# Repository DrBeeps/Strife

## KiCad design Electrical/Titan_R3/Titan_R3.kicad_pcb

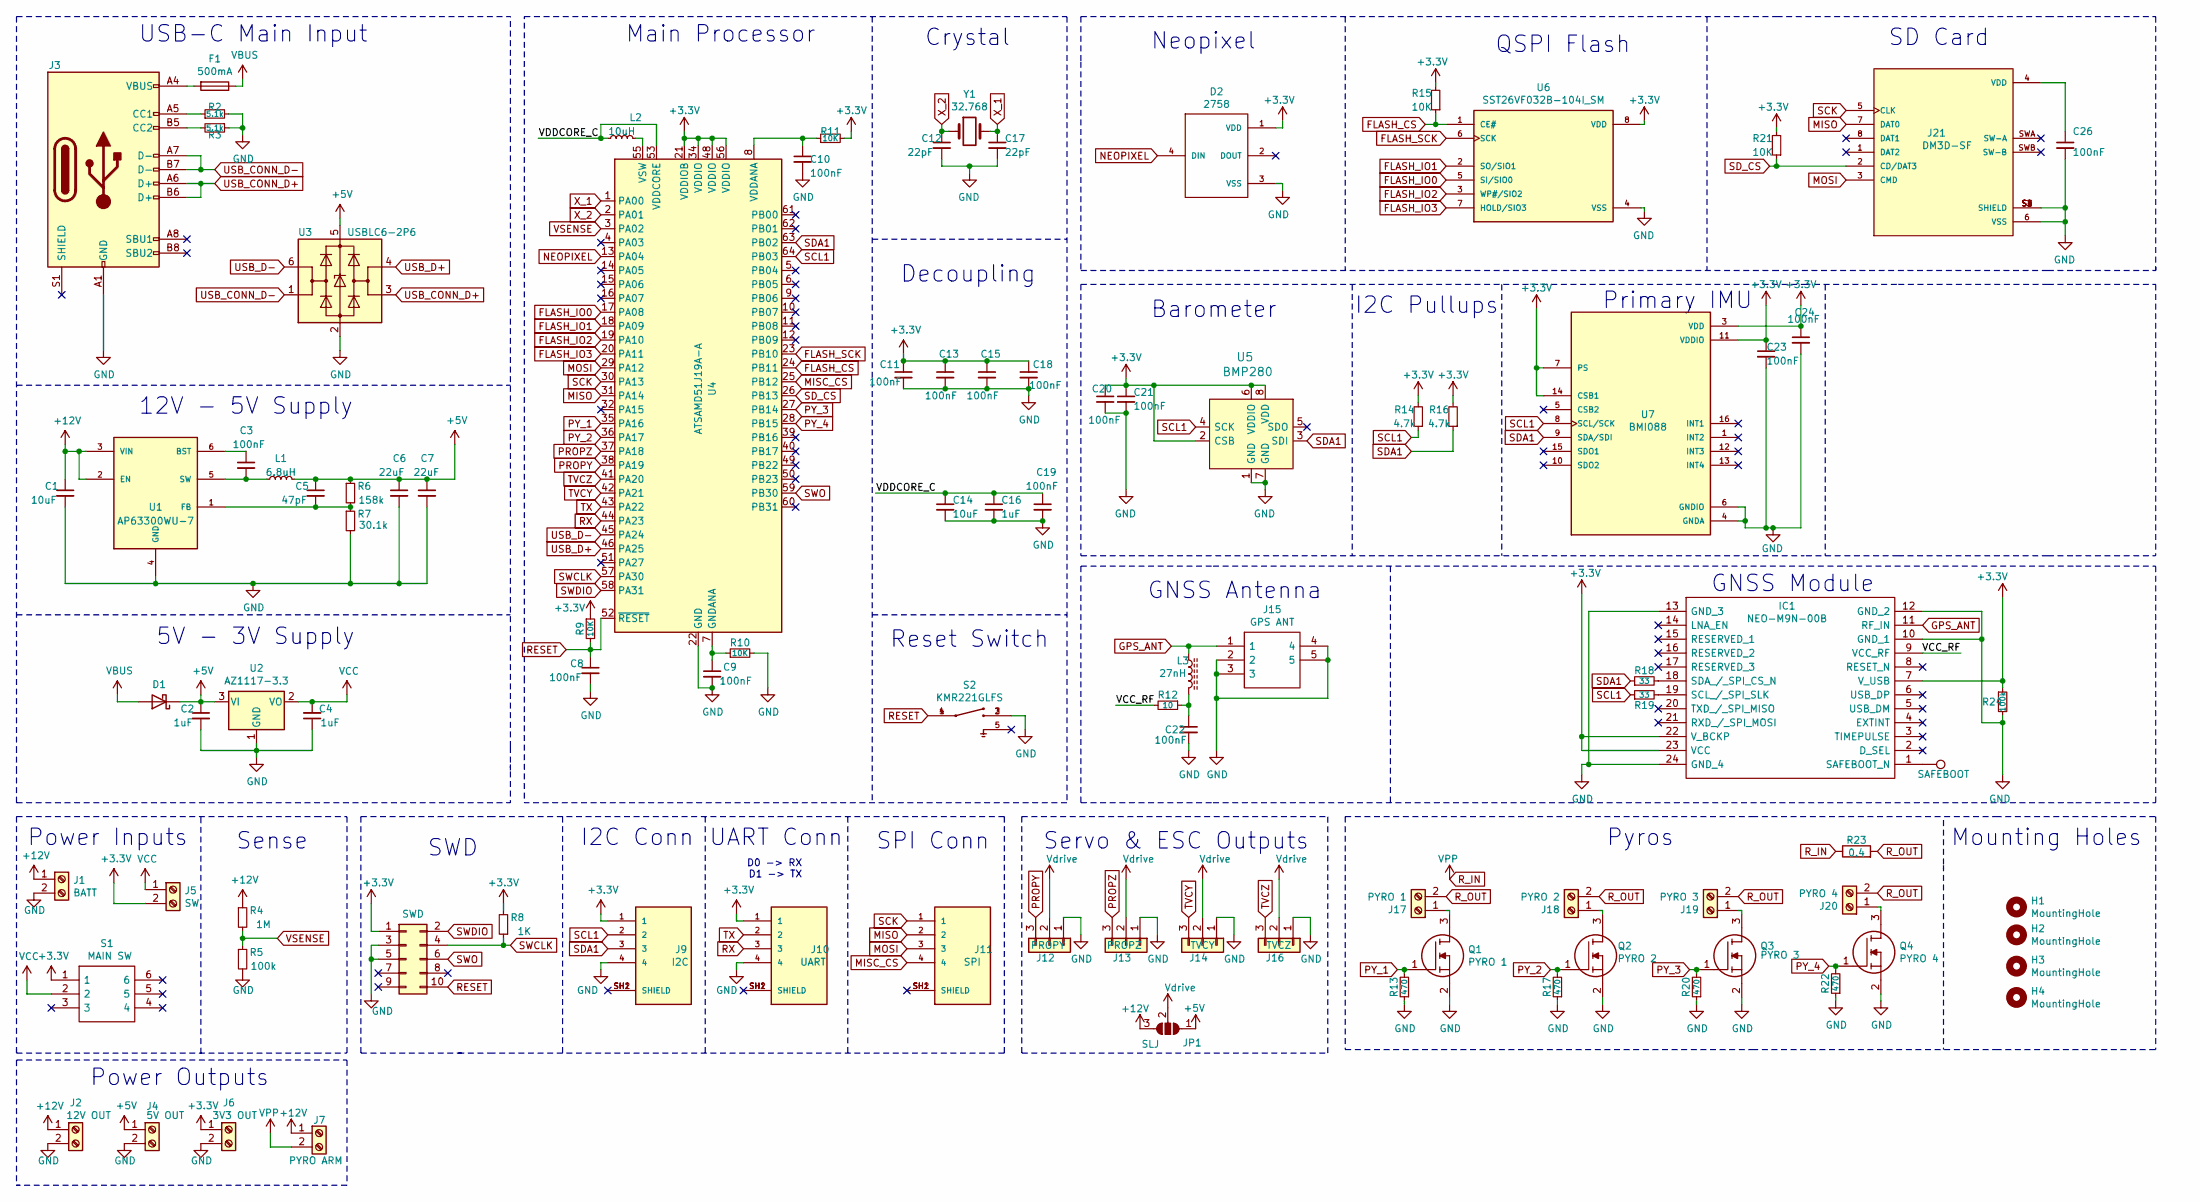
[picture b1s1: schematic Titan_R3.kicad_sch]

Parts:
C1, C14: 10uF; C_0805_2012Metric
C2, C4, C16: 1uF; C_0603_1608Metric
C3, C8, C9, C10, C11, C13, C15, C18, C19, C20, C21, C22, C23, C24, C26: 100nF; C_0603_1608Metric
C5: 47pF; C_0603_1608Metric
C6, C7: 22uF; C_0805_2012Metric
C12, C17: 22pF; C_0603_1608Metric
D1: D_Schottky; D_SOD-323
D2: 2758; PARTREV 01
F1: 500mA; Fuse_0603_1608Metric
H1, H2, H3, H4: MountingHole; MountingHole_3mm
IC1: NEO-M9N-00B; NEOM9N00B; Manufacturer_Part_Number NEO-M9N-00B; Mouser Part Number 377-NEO-M9N-00B
J1: BATT; TerminalBlock_4Ucon_1x02_P3.50mm_Vertical
J2: 12V OUT; TerminalBlock_4Ucon_1x02_P3.50mm_Vertical
J3: USB_C_Receptacle_USB2.0; USB_C_Receptacle_HRO_TYPE-C-31-M-12
J4: 5V OUT; TerminalBlock_4Ucon_1x02_P3.50mm_Vertical
J5: SW; TerminalBlock_4Ucon_1x02_P3.50mm_Vertical
J6: 3V3 OUT; TerminalBlock_4Ucon_1x02_P3.50mm_Vertical
J7: PYRO ARM; TerminalBlock_4Ucon_1x02_P3.50mm_Vertical
J8: SWD; PinHeader_2x05_P1.27mm_Vertical_SMD
J9: I2C; JST_SM04B-GHS-TB(LF)(SN)-; PARTREV NA
J10: UART; JST_SM04B-GHS-TB(LF)(SN)-; PARTREV NA
J11: SPI; JST_SM04B-GHS-TB(LF)(SN)-; PARTREV NA
J12: PROPY; PinHeader_1x03_P2.54mm_Vertical
J13: PROPZ; PinHeader_1x03_P2.54mm_Vertical
J14: TVCY; PinHeader_1x03_P2.54mm_Vertical
J15: GPS ANT; CONSMA001CG; Manufacturer_Part_Number CONSMA001-C-G; Mouser Part Number 712-CONSMA001-C-G
J16: TVCZ; PinHeader_1x03_P2.54mm_Vertical
J17: PYRO 1; TerminalBlock_4Ucon_1x02_P3.50mm_Vertical
J18: PYRO 2; TerminalBlock_4Ucon_1x02_P3.50mm_Vertical
J19: PYRO 3; TerminalBlock_4Ucon_1x02_P3.50mm_Vertical
J20: PYRO 4; TerminalBlock_4Ucon_1x02_P3.50mm_Vertical
J21: DM3D-SF; HRS_DM3D-SF; PARTREV 2017.1
JP1: SLJ; SolderJumper-3_P1.3mm_Open_Pad1.0x1.5mm
L1: 6.8uH; INDPM7366X300N
L2: 10uH; L_0805_2012Metric
L3: 27nH; L_0603_1608Metric
Q1: PYRO 1; SOT65P210X110-3N; Manufacturer_Part_Number DMN2058UW-7; Mouser Part Number 621-DMN2058UW-7
Q2: PYRO 2; SOT65P210X110-3N; Manufacturer_Part_Number DMN2058UW-7; Mouser Part Number 621-DMN2058UW-7
Q3: PYRO 3; SOT65P210X110-3N; Manufacturer_Part_Number DMN2058UW-7; Mouser Part Number 621-DMN2058UW-7
Q4: PYRO 4; SOT65P210X110-3N; Manufacturer_Part_Number DMN2058UW-7; Mouser Part Number 621-DMN2058UW-7
R2, R3: 5.1k; R_0603_1608Metric
R4: 1M; R_0603_1608Metric
R5, R24: 100k; R_0603_1608Metric
R6: 158k; R_0603_1608Metric
R7: 30.1k; R_0603_1608Metric
R8: 1K; R_0603_1608Metric
R9, R10, R11, R15, R21: 10K; R_0603_1608Metric
R12: 10; R_0603_1608Metric
R13, R17, R20, R22: 470; R_0603_1608Metric
R14, R16: 4.7k; R_0603_1608Metric
R18, R19: 33; R_0603_1608Metric
R23: 0.4; PWR163S25R400FE
S1: MAIN SW; JS202011SCQN; Manufacturer_Part_Number JS202011SCQN; Mouser Part Number 611-JS202011SCQN
S2: KMR221GLFS; SW_KMR221GLFS
TP1: SAFEBOOT; TestPoint_Pad_D1.0mm
U1: AP63300WU-7; SOT95P280X90-6N; PARTREV 2020-04-24
U2: AZ1117-3.3; SOT-223
U3: USBLC6-2P6; SOT-666
U4: ATSAMD51J19A-A; TQFP-64_10x10mm_P0.5mm
U5: BMP280; LGA-8_2x2.5mm_BMP280; MPN BMP280; Digi-Key_PN 828-1064-1-ND
U6: SST26VF032B-104I_SM
U7: BMI088; PARTREV 1.4_092018
Y1: 32.768; CRYSTAL_ECS

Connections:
+3V3: C11.1, C13.1, C15.1, C18.1, C20.1, C21.1, C23.1, C24.1, D2.1 (VDD), IC1.7 (V_USB), IC1.22 (V_BCKP), IC1.23 (VCC), J5.2, J6.1, J8.1, J9.1, J10.1, R8.2, R9.1, R11.2, R14.2, R15.2, R16.2, R21.2, R24.1, S1.1, U4.21 (VDDIOB), U4.34 (VDDIO), U4.48 (VDDIO), U4.56 (VDDIO), U5.2 (CSB), U5.6 (VDDIO), U5.8 (VDD), U6.8 (VDD), U7.3 (VDD), U7.7 (PS), U7.11 (VDDIO), U7.14 (CSB1)
+5V: C2.1, C5.1, C6.1, C7.1, D1.1 (K), J4.1, JP1.1 (A), L1.2, R6.1, U2.3 (VI), U3.5 (VBUS)
+12V: C1.1, J1.1, J2.1, J7.1, JP1.3 (B), R4.1, U1.2 (EN), U1.3 (VIN)
/VCC_RF: IC1.9 (VCC_RF), R12.2
/VDDCORE_C: C14.1, C16.1, C19.1, L2.1, U4.53 (VDDCORE)
FLASH_CS: R15.1, U4.24 (PB11), U6.1 (CE#)
FLASH_IO0: U4.17 (PA08), U6.5 (SI/SIO0)
FLASH_IO1: U4.18 (PA09), U6.2 (SO/SIO1)
FLASH_IO2: U4.19 (PA10), U6.3 (WP#/SIO2)
FLASH_IO3: U4.20 (PA11), U6.7 (HOLD/SIO3)
FLASH_SCK: U4.23 (PB10), U6.6 (SCK)
GND: C1.2, C2.2, C4.1, C6.2, C7.2, C8.2, C9.2, C10.2, C11.2, C12.2, C13.2, C14.2, C15.2, C16.2, C17.2, C18.2, C19.2, C20.2, C21.2, C22.2, C23.2, C24.2, C26.2, D2.3 (VSS), IC1.10 (GND_1), IC1.12 (GND_2), IC1.13 (GND_3), IC1.24 (GND_4), J1.2, J2.2, J3.A1 (GND), J3.A12 (GND), J3.B1 (GND), J3.B12 (GND), J4.2, J6.2, J8.3, J8.5, J9.4, J10.4, J12.1, J13.1, J14.1, J15.2, J15.3, J15.4, J15.5, J16.1, J21.6 (VSS), J21.S1 (SHIELD), J21.S2 (SHIELD), J21.S3 (SHIELD), J21.S4 (SHIELD), Q1.2, Q2.2, Q3.2, Q4.2, R2.2, R3.1, R5.2, R7.2, R10.2, R13.1, R17.1, R20.1, R22.1, R24.2, S2.2, S2.3, U1.4 (GND), U2.1 (GND), U3.2 (GND), U4.22 (GND), U4.33 (GND), U4.47 (GND), U4.54 (GND), U5.1 (GND), U5.7 (GND), U6.4 (VSS), U7.4 (GNDA), U7.6 (GNDIO)
GPS_ANT: IC1.11 (RF_IN), J15.1, L3.1
MISC_CS: J11.4, U4.25 (PB12)
MISO: J11.2, J21.7 (DAT0), U4.31 (PA14)
MOSI: J11.3, J21.3 (CMD), U4.29 (PA12)
NEOPIXEL: D2.4 (DIN), U4.13 (PA04)
unnamed: C3.1, U1.6 (BST)
unnamed: C3.2, L1.1, U1.5 (SW)
unnamed: C5.2, R6.2, R7.1, U1.1 (FB)
unnamed: C9.1, R10.1, U4.7 (GNDANA)
unnamed: C10.1, R11.1, U4.8 (VDDANA)
unnamed: C22.1, L3.2, R12.1
unnamed: C26.1, J21.4 (VDD)
unnamed: F1.2, J3.A4 (VBUS), J3.A9 (VBUS), J3.B4 (VBUS), J3.B9 (VBUS)
unnamed: IC1.1 (SAFEBOOT_N), TP1.1
unnamed: IC1.18 (SDA_/_SPI_CS_N), R18.2
unnamed: IC1.19 (SCL_/_SPI_SLK), R19.2
unnamed: J3.A5 (CC1), R2.1
unnamed: J3.B5 (CC2), R3.2
unnamed: J17.1, Q1.3
unnamed: J18.1, Q2.3
unnamed: J19.1, Q3.3
unnamed: J20.1, Q4.3
unnamed: L2.2, U4.55 (VSW)
PROPY: J12.3, U4.38 (PA19)
PROPZ: J13.3, U4.37 (PA18)
PY_1: Q1.1, R13.2, U4.35 (PA16)
PY_2: Q2.1, R17.2, U4.36 (PA17)
PY_3: Q3.1, R20.2, U4.27 (PB14)
PY_4: Q4.1, R22.2, U4.28 (PB15)
RESET: C8.1, J8.10, R9.2, S2.1, S2.4, U4.52 (~RESET)
RX: J10.3, U4.44 (PA23)
R_IN: J7.2, R23.1
R_OUT: J17.2, J18.2, J19.2, J20.2, R23.2
SCK: J11.1, J21.5 (CLK), U4.30 (PA13)
SCL1: J9.2, R14.1, R19.1, U4.64 (PB03), U5.4 (SCK), U7.8 (SCL/SCK)
SDA1: J9.3, R16.1, R18.1, U4.63 (PB02), U5.3 (SDI), U7.9 (SDA/SDI)
SD_CS: J21.2 (CD/DAT3), R21.1, U4.26 (PB13)
SWCLK: J8.4, R8.1, U4.57 (PA30)
SWDIO: J8.2, U4.58 (PA31)
SWO: J8.6, U4.59 (PB30)
TVCY: J14.3, U4.42 (PA21)
TVCZ: J16.3, U4.41 (PA20)
TX: J10.2, U4.43 (PA22)
USB_CONN_D+: J3.A6 (D+), J3.B6 (D+), U3.3 (I/O2)
USB_CONN_D-: J3.A7 (D-), J3.B7 (D-), U3.1 (I/O1)
USB_D+: U3.4 (I/O2), U4.46 (PA25)
USB_D-: U3.6 (I/O1), U4.45 (PA24)
VBUS: D1.2 (A), F1.1
VCC: C4.2, J5.1, S1.2, U2.2 (VO)
VSENSE: R4.2, R5.1, U4.3 (PA02)
Vdrive: J12.2, J13.2, J14.2, J16.2, JP1.2 (C)
X_1: C17.1, U4.1 (PA00), Y1.2
X_2: C12.1, U4.2 (PA01), Y1.1

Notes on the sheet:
Power Inputs
Power Outputs
USB-C Main Input
12V - 5V Supply
5V - 3V Supply
Sense
SWD
I2C Conn
Main Processor
UART Conn
D0 -> RX D1 -> TX
SPI Conn
Reset Switch
Decoupling
Crystal
Servo & ESC Outputs
GNSS Antenna
Neopixel
Barometer
I2C Pullups
QSPI Flash
Primary IMU
Pyros
GNSS Module
SD Card
Mounting Holes

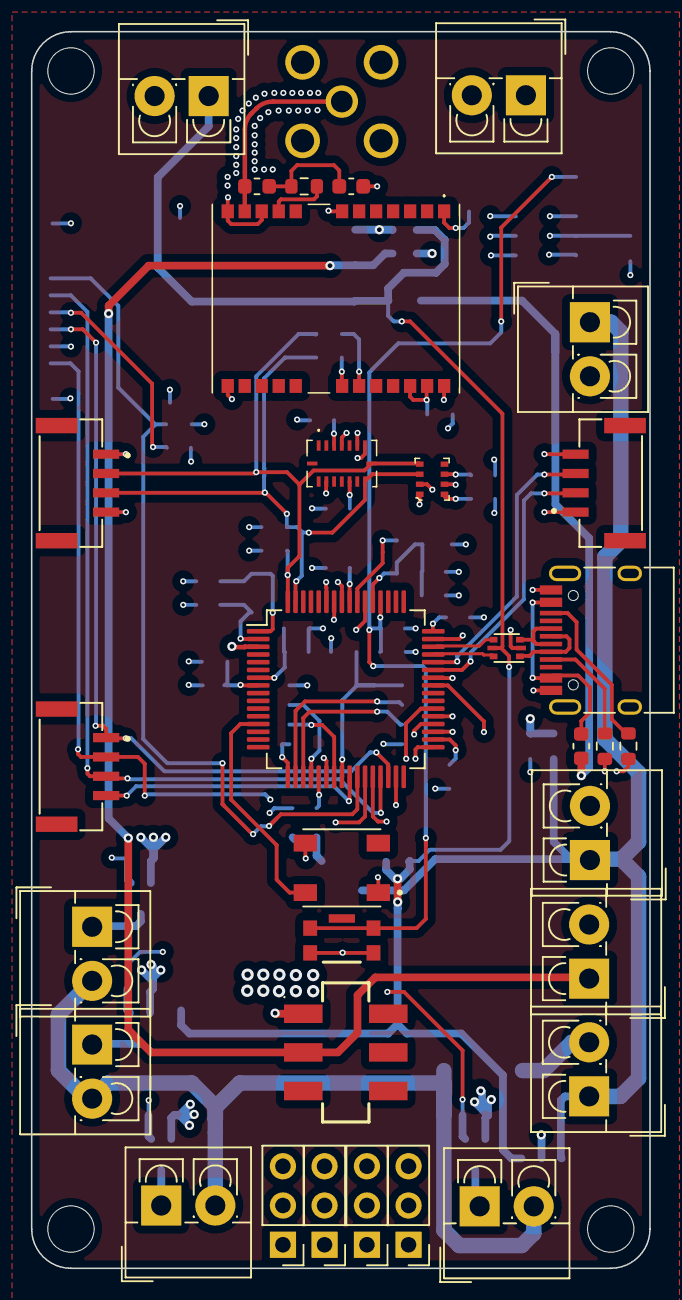
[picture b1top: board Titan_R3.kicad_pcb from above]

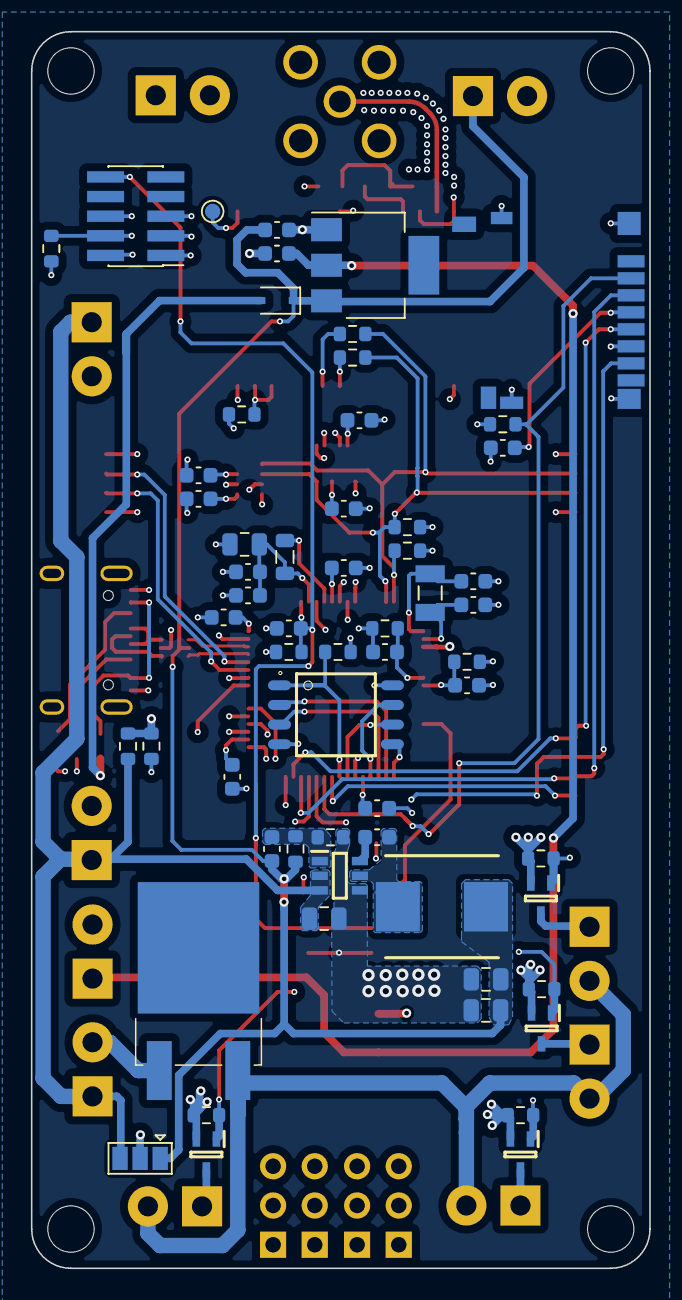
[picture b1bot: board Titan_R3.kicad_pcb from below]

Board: 4 copper layers, 40.0 x 80.0 mm, 96 parts (59 on the bottom side), 65 nets.

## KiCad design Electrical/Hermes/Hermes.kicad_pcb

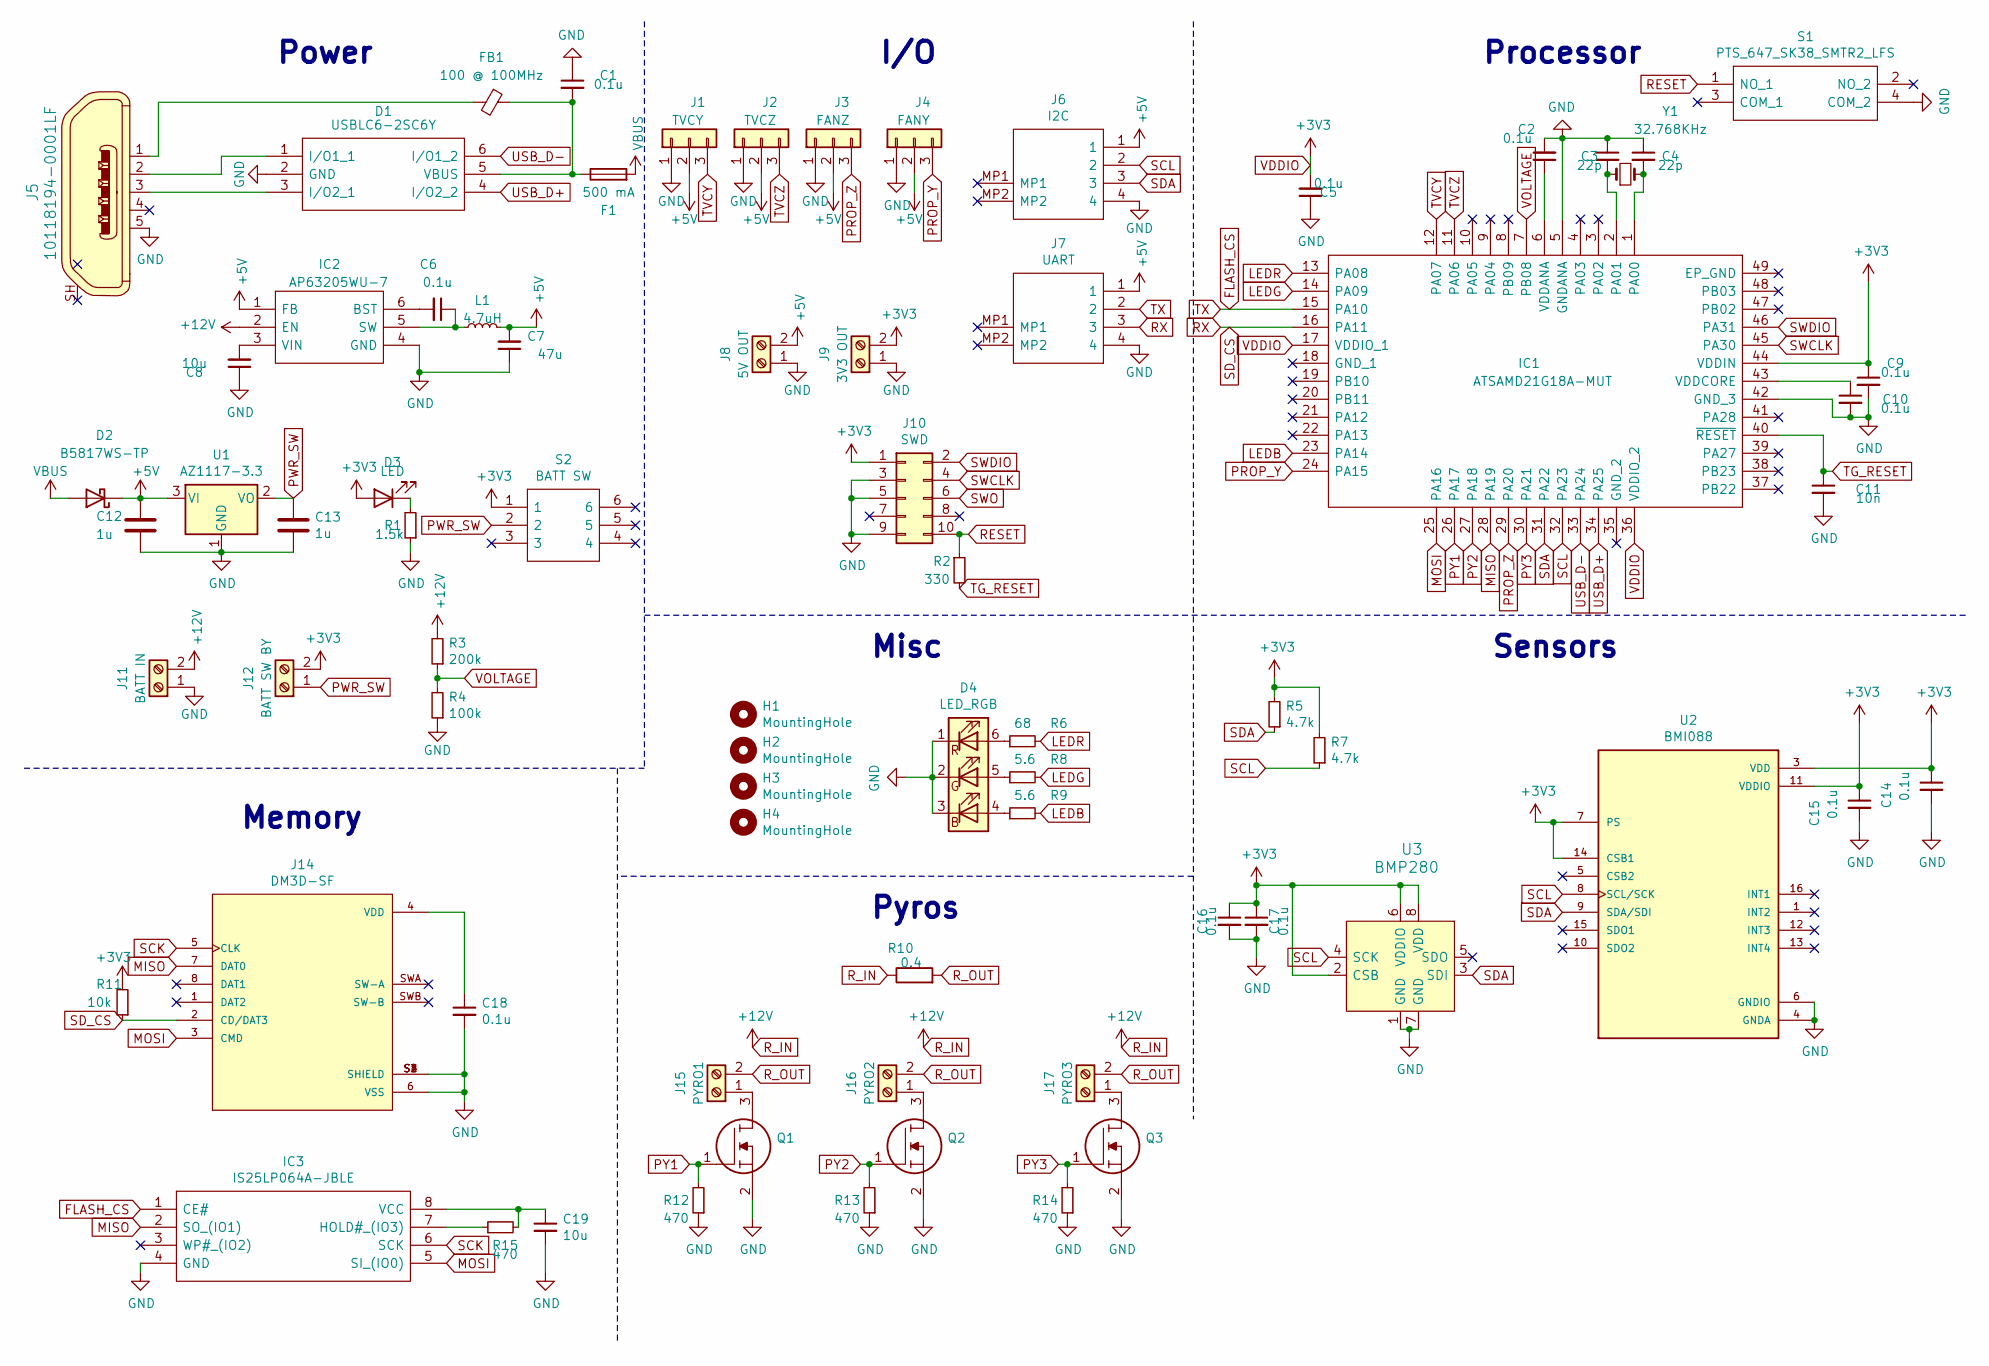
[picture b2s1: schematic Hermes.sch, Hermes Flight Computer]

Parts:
C1, C6: 0.1u; C_0805_2012Metric
C2, C5, C9, C10, C14, C15, C16, C17, C18: 0.1u; C_0603_1608Metric
C3, C4: 22p; C_0603_1608Metric
C7: 47u; C_1206_3216Metric
C8, C19: 10u; C_0805_2012Metric
C11: 10n; C_0603_1608Metric
C12, C13: 1u; C_0805_2012Metric
D1: USBLC6-2SC6Y; SOT23-6L; Manufacturer_Part_Number USBLC6-2SC6Y; Mouser Part Number 511-USBLC6-2SC6Y
D2: B5817WS-TP; D_SOD-323
D3: LED; LED_0805_2012Metric_Pad1.15x1.40mm_HandSolder
D4: LED_RGB; 150352M173300
F1: 500 mA; Fuse_0805_2012Metric
FB1: 100 @ 100MHz; L_0603_1608Metric
H1, H2, H3, H4: MountingHole; MountingHole_3.2mm_M3
IC1: ATSAMD21G18A-MUT; Manufacturer_Part_Number ATSAMD21G18A-MUT; Mouser Part Number 556-ATSAMD21G18A-MUT
IC2: AP63205WU-7; TSOT-23-6; Manufacturer_Part_Number AP63205WU-7; Mouser Part Number 621-AP63205WU-7
IC3: IS25LP064A-JBLE; SOIC127P790X216-8N; Manufacturer_Part_Number IS25LP064A-JBLE; Mouser Part Number N/A
J1: TVCY; PinHeader_1x03_P2.54mm_Vertical
J2: TVCZ; PinHeader_1x03_P2.54mm_Vertical
J3: FANZ; PinHeader_1x03_P2.54mm_Vertical
J4: FANY; PinHeader_1x03_P2.54mm_Vertical
J5: 10118194-0001LF; AMPHENOL_10118194-0001LF; MPN 10118194-0001LF; Digi-Key_PN 609-4618-1-ND
J6: I2C; 0532617004; Manufacturer_Part_Number 0532617004
J7: UART; 0532617004; Manufacturer_Part_Number 0532617004
J8: 5V OUT; TerminalBlock_4Ucon_1x02_P3.50mm_Vertical
J9: 3V3 OUT; TerminalBlock_4Ucon_1x02_P3.50mm_Vertical
J10: SWD; PinHeader_2x05_P1.27mm_Vertical_SMD
J11: BATT IN; TerminalBlock_4Ucon_1x02_P3.50mm_Vertical
J12: BATT SW BY; TerminalBlock_4Ucon_1x02_P3.50mm_Vertical
J14: DM3D-SF; HRS_DM3D-SF; PARTREV 2017.1
J15: PYRO1; TerminalBlock_4Ucon_1x02_P3.50mm_Vertical
J16: PYRO2; TerminalBlock_4Ucon_1x02_P3.50mm_Vertical
J17: PYRO3; TerminalBlock_4Ucon_1x02_P3.50mm_Vertical
L1: 4.7uH; IND_ECS-MPI4040R2-4R7-R
Q1, Q2, Q3: SOT-23-3; Manufacturer_Part_Number DMN2058UW-7; Mouser Part Number 621-DMN2058UW-7
R1: 1.5k; R_0603_1608Metric
R2: 330; R_0603_1608Metric
R3: 200k; R_0603_1608Metric
R4: 100k; R_0603_1608Metric
R5, R7: 4.7k; R_0603_1608Metric
R6: 68; R_0603_1608Metric
R8, R9: 5.6; R_0603_1608Metric
R10: 0.4; PWR163S25R400FE
R11: 10k; R_0603_1608Metric
R12, R13, R14, R15: 470; R_0603_1608Metric
S1: PTS_647_SK38_SMTR2_LFS; PTS647SK38SMTR2LFS; Manufacturer_Part_Number PTS 647 SK38 SMTR2 LFS
S2: BATT SW; JS202011SCQN; Manufacturer_Part_Number JS202011SCQN; Mouser Part Number 611-JS202011SCQN
U1: AZ1117-3.3; SOT-223
U2: BMI088; PARTREV 1.4_092018
U3: BMP280; LGA-8_2x2.5mm_BMP280; MPN BMP280; Digi-Key_PN 828-1064-1-ND
Y1: 32.768KHz; CRYSTAL_ECS

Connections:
+5V: C7.2, C12.1, D2.1 (K), IC2.1 (FB), J1.2, J2.2, J3.2, J4.2, J6.1, J7.1, J8.2, L1.2, U1.3 (VI)
FLASH_CS: IC1.15 (PA10), IC3.1 (CE#), J7.2
GND: C1.1, C2.2, C3.1, C4.1, C5.1, C7.1, C8.1, C9.2, C10.2, C11.2, C12.2, C13.2, C14.2, C15.2, C16.2, C17.2, C18.2, C19.2, D1.2 (GND), D4.1 (RK), D4.2 (GK), D4.3 (BK), IC1.5 (GNDANA), IC1.42 (GND_3), IC2.4 (GND), IC3.4 (GND), J1.1, J2.1, J3.1, J4.1, J5.5, J6.4, J7.4, J8.1, J9.1, J10.3, J10.5, J10.9, J11.1, J14.6 (VSS), J14.S1 (SHIELD), J14.S2 (SHIELD), J14.S3 (SHIELD), J14.S4 (SHIELD), Q1.2, Q2.2, Q3.2, R1.1, R4.1, R12.1, R13.1, R14.1, S1.4 (COM_2), U1.1 (GND), U2.4 (GNDA), U2.6 (GNDIO), U3.1 (GND), U3.7 (GND)
LEDB: IC1.23 (PA14), R9.2
LEDG: IC1.14 (PA09), R8.2
LEDR: IC1.13 (PA08), R6.2
MISO: IC1.28 (PA19), IC3.2 (SO_(IO1)), J14.7 (DAT0)
MOSI: IC1.25 (PA16), IC3.5 (SI_(IO0)), J14.3 (CMD)
unnamed: C1.2, D1.5 (VBUS), F1.1, FB1.1
unnamed: C2.1, IC1.6 (VDDANA)
unnamed: C3.2, IC1.2 (PA01), Y1.1
unnamed: C4.2, IC1.1 (PA00), Y1.2
unnamed: C6.1, IC2.5 (SW), L1.1
unnamed: C6.2, IC2.6 (BST)
unnamed: C8.2, IC2.3 (VIN)
unnamed: C10.1, IC1.43 (VDDCORE)
unnamed: C18.1, J14.4 (VDD)
unnamed: C19.1, IC3.8 (VCC), R15.2
unnamed: D1.1 (I/O1_1), J5.2
unnamed: D1.3 (I/O2_1), J5.3
unnamed: D3.1 (K), R1.2
unnamed: D4.4 (BA), R9.1
unnamed: D4.5 (GA), R8.1
unnamed: D4.6 (RA), R6.1
unnamed: FB1.2, J5.1
unnamed: IC3.7 (HOLD#_(IO3)), R15.1
unnamed: J15.1, Q1.3
unnamed: J16.1, Q2.3
unnamed: J17.1, Q3.3
PROP_Y: IC1.24 (PA15), J4.3
PROP_Z: IC1.29 (PA20), J3.3
PWR_SW: C13.1, J12.1, S2.2, U1.2 (VO)
PY1: IC1.26 (PA17), Q1.1, R12.2
PY2: IC1.27 (PA18), Q2.1, R13.2
PY3: IC1.30 (PA21), Q3.1, R14.2
RESET: J10.10, R2.1, S1.1 (NO_1)
RX: IC1.16 (PA11), J7.3, J14.2 (CD/DAT3), R11.1
R_IN: IC2.2 (EN), J11.2, R3.2, R10.1
R_OUT: J15.2, J16.2, J17.2, R10.2
SCK: IC3.6 (SCK), J14.5 (CLK)
SCL: IC1.32 (PA23), J6.2, R7.1, U2.8 (SCL/SCK), U3.4 (SCK)
SDA: IC1.31 (PA22), J6.3, R5.1, U2.9 (SDA/SDI), U3.3 (SDI)
SWCLK: IC1.45 (PA30), J10.4
SWDIO: IC1.46 (PA31), J10.2
SWO: J10.6
TG_RESET: C11.1, IC1.40 (~RESET), R2.2
TVCY: IC1.12 (PA07), J1.3
TVCZ: IC1.11 (PA06), J2.3
USB_D+: D1.4 (I/O2_2), IC1.34 (PA25)
USB_D-: D1.6 (I/O1_2), IC1.33 (PA24)
VBUS: D2.2 (A), F1.2
VDDIO: C5.2, C9.1, C14.1, C15.1, C16.1, C17.1, D3.2 (A), IC1.17 (VDDIO_1), IC1.36 (VDDIO_2), IC1.44 (VDDIN), J9.2, J10.1, J12.2, R5.2, R7.2, R11.2, S2.1, U2.3 (VDD), U2.7 (PS), U2.11 (VDDIO), U2.14 (CSB1), U3.2 (CSB), U3.6 (VDDIO), U3.8 (VDD)
VOLTAGE: IC1.7 (PB08), R3.1, R4.2

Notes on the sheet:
Power
I/O
Processor
Misc
Memory
Pyros
Sensors

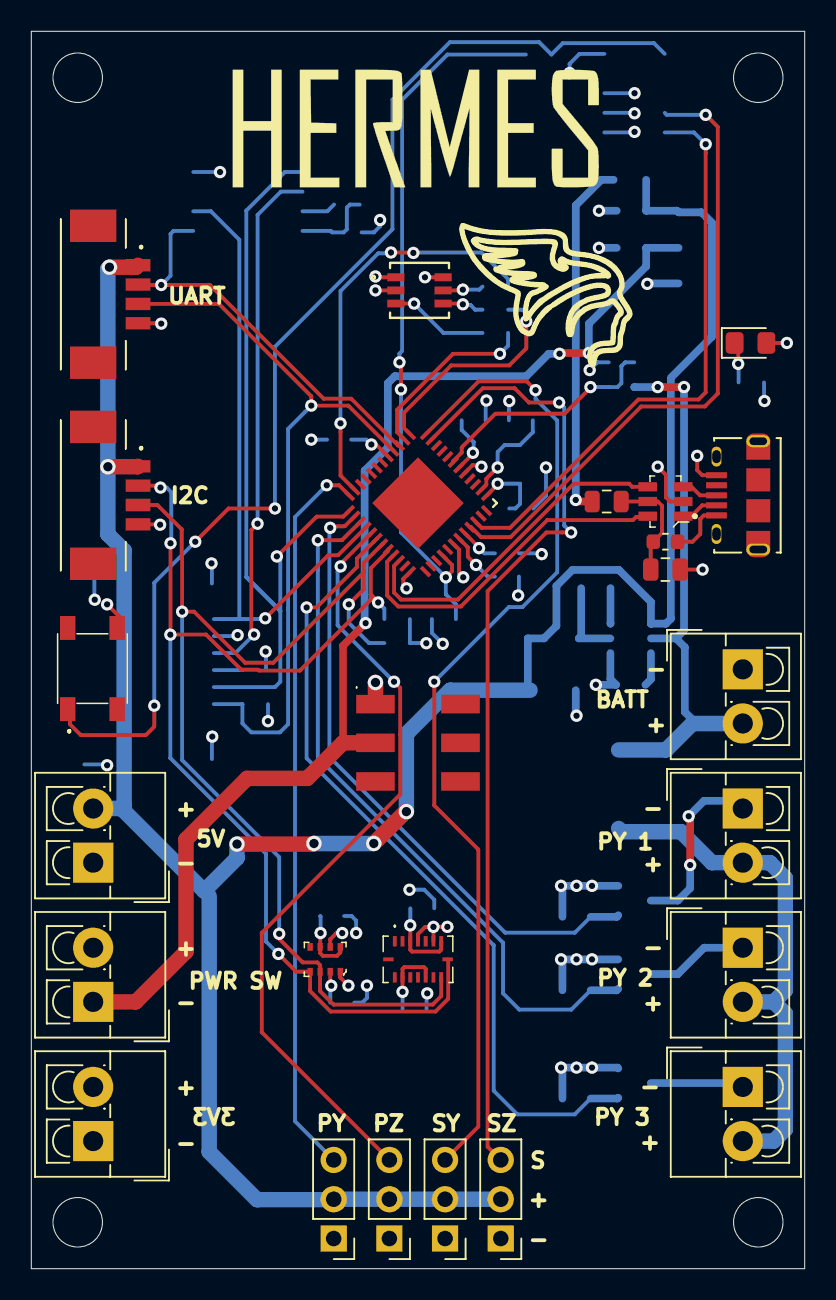
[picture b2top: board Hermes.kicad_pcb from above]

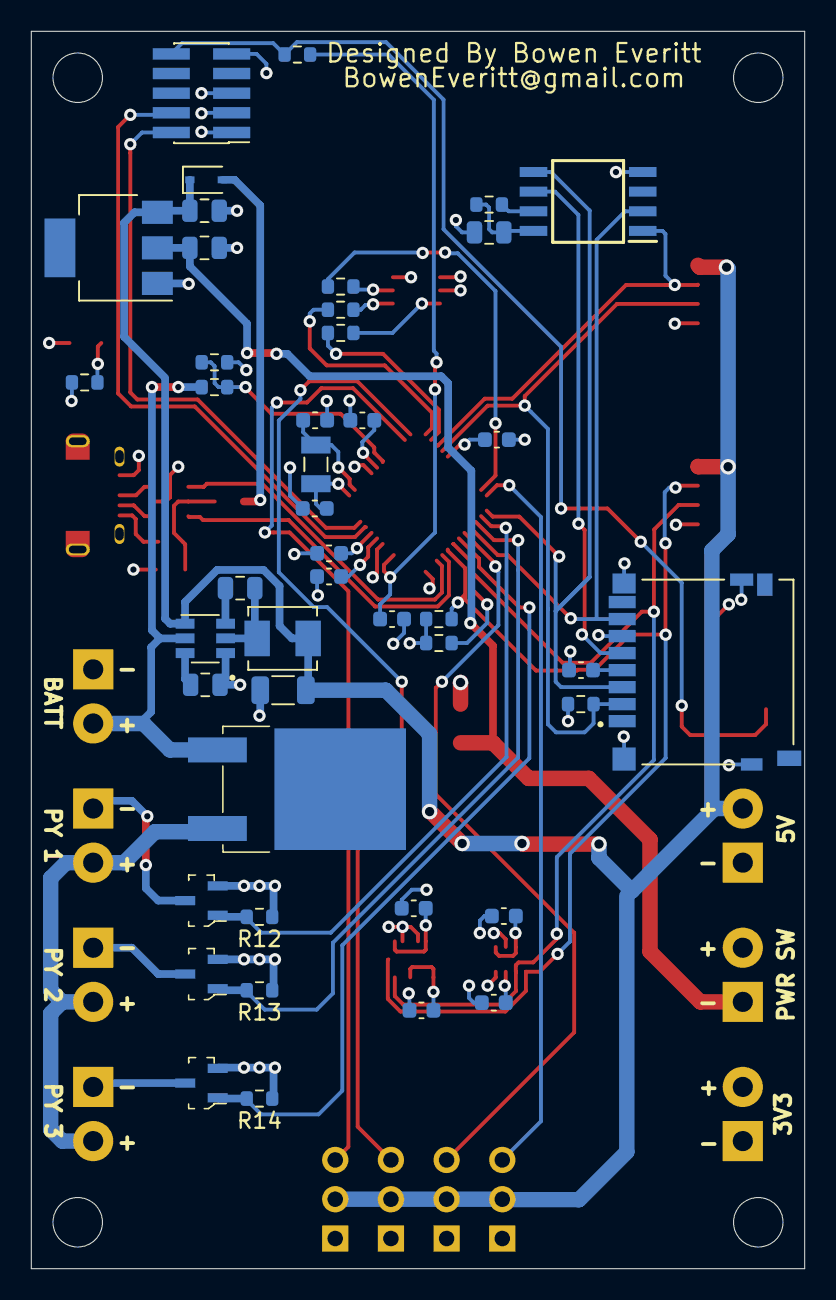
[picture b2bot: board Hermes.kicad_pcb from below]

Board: 4 copper layers, 50.0 x 80.0 mm, 73 parts (44 on the bottom side), 52 nets.

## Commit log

2021-03-12 worked more on routing
2021-04-13 major flight software changes
2021-04-18 added a ton of software
2021-04-21 big software updates
    updates n' stuff
2021-04-22 moar updates

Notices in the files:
parts and their libraries:
Copyright 2016 Accelerated Designs. All rights reserved.
